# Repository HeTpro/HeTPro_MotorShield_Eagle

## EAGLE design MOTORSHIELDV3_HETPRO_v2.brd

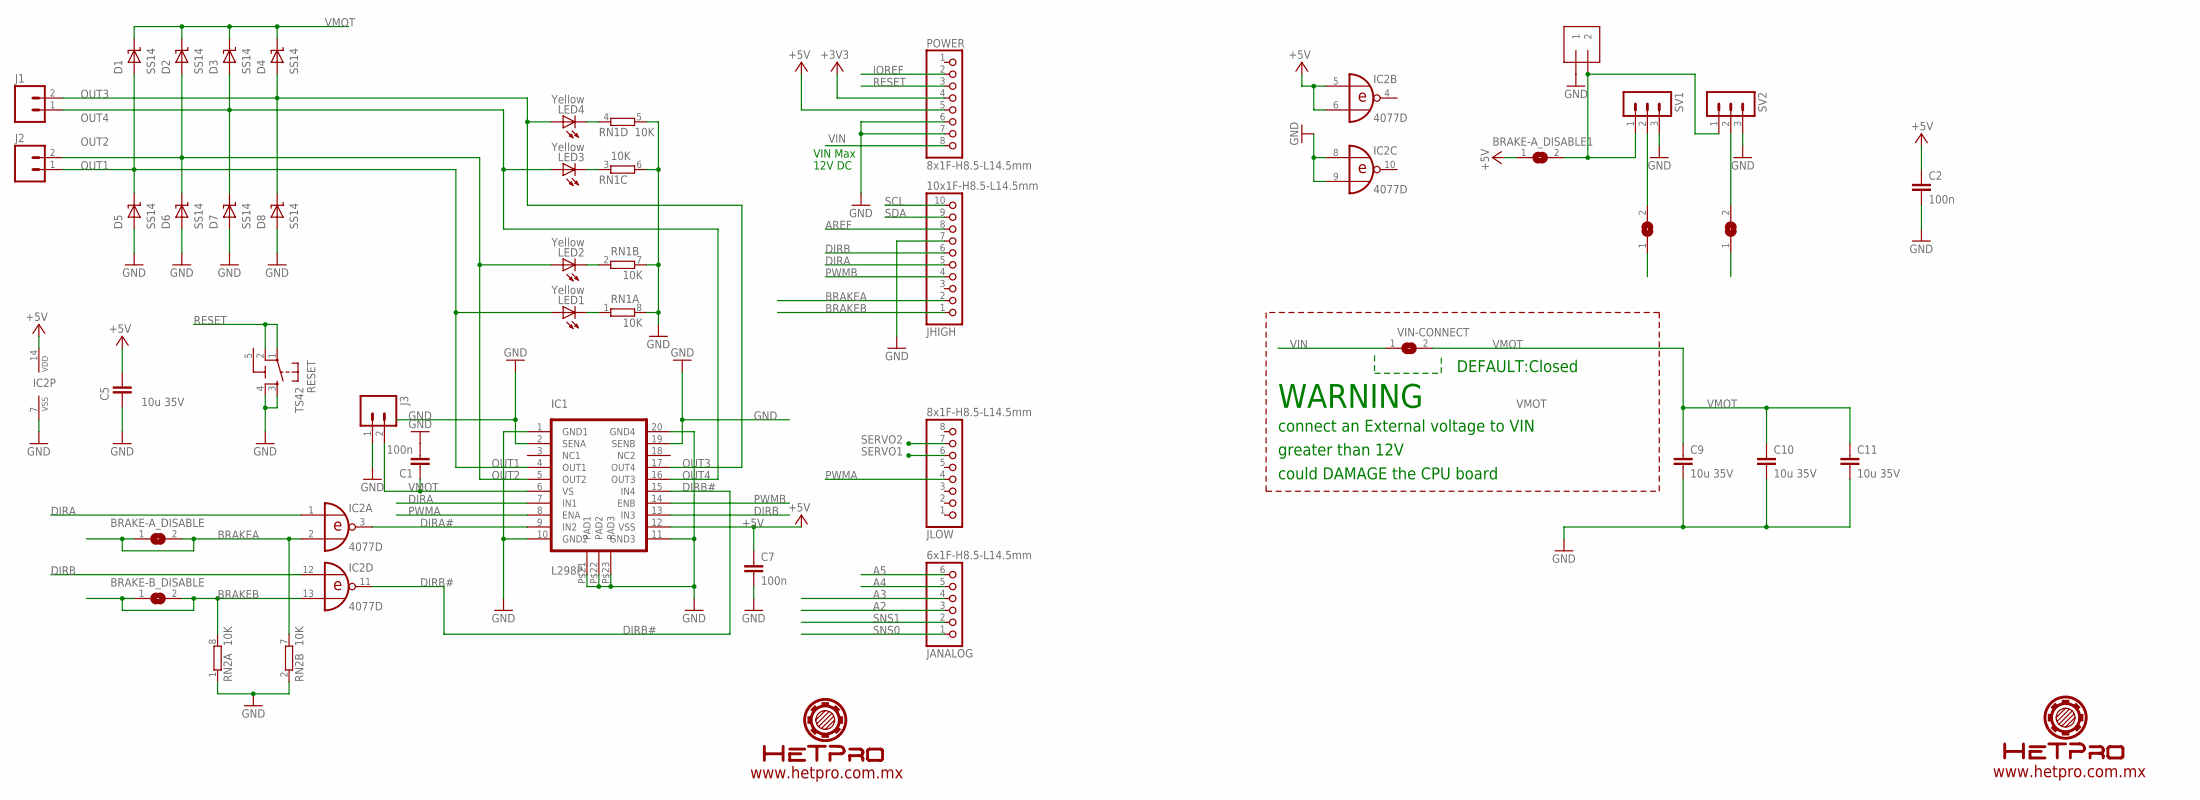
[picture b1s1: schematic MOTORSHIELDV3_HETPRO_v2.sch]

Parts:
BRAKE-A_DISABLE, BRAKE-A_DISABLE1, BRAKE-A_DISABLE2, BRAKE-A_DISABLE3: SJ
BRAKE-B_DISABLE: SJ
C1, C2, C7: 100n; C0603
C5, C9, C10, C11: 10u 35V; C1210
D1, D2, D3, D4, D5, D6, D7, D8: SS14; SMA
IC1: L298P; POWER-SO20
IC2: 4077D; SO14
J1, J2, J3: M025MM; SCREWTERMINAL-5MM-2
J4: 1X2-3.5MM
JANALOG: 6x1F-H8.5-L14.5mm; 1X06-TH
JHIGH: 10x1F-H8.5-L14.5mm; 1X10-TH
JLOW: 8x1F-H8.5-L14.5mm; 1X08-TH
LED1, LED2, LED3, LED4: Yellow; LED-1206
POWER: 8x1F-H8.5-L14.5mm; 1X08-TH
RESET: TS42
RN1, RN2: 10K; CAY16
SV1, SV2: MA03-1
VIN-CONNECT: SJ

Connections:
5-GND: RESET.5 (5-GND)
+3V3: POWER.4
+5V: BRAKE-A_DISABLE1.1, C2.1, C5.1, C7.1, IC1.P$12 (VSS), IC2.5 (I0), IC2.6 (I1), IC2.14 (VDD), POWER.5
A2: JANALOG.3
A3: JANALOG.4
A4: JANALOG.5
A5: JANALOG.6
AREF: JHIGH.8
BRAKEA: BRAKE-A_DISABLE.1, BRAKE-A_DISABLE.2, IC2.2 (I1), JHIGH.2, RN2.7 (2)
BRAKEB: BRAKE-B_DISABLE.1, BRAKE-B_DISABLE.2, IC2.13 (I1), JHIGH.1, RN2.8 (2)
DIRA: IC1.P$7 (IN1), IC2.1 (I0), JHIGH.5
DIRA#: IC1.P$9 (IN2), IC2.3 (O)
DIRB: IC1.P$13 (IN3), IC2.12 (I0), JHIGH.6
DIRB#: IC1.P$15 (IN4), IC2.11 (O)
GND: C1.2, C2.2, C5.2, C7.2, C9.2, C10.2, C11.2, D5.P$2 (A), D6.P$2 (A), D7.P$2 (A), D8.P$2 (A), IC1.P$1 (GND1), IC1.P$2 (SENA), IC1.P$10 (GND2), IC1.P$11 (GND3), IC1.P$19 (SENB), IC1.P$20 (GND4), IC1.P$21 (PAD1), IC1.P$22 (PAD2), IC1.P$23 (PAD3), IC2.7 (VSS), IC2.8 (I0), IC2.9 (I1), J3.1, J4.1, JHIGH.7, POWER.6, POWER.7, RESET.3, RESET.4, RN1.5 (2), RN1.6 (2), RN1.7 (2), RN1.8 (2), RN2.1, RN2.2 (1), SV1.3, SV2.3
IOREF: POWER.2
unnamed: LED4.C, RN1.4 (1)
unnamed: LED3.C, RN1.3 (1)
unnamed: LED2.C, RN1.2 (1)
unnamed: LED1.C, RN1.1
unnamed: BRAKE-A_DISABLE1.2, J4.2, SV1.1, SV2.1
unnamed: BRAKE-A_DISABLE2.2, SV1.2
unnamed: BRAKE-A_DISABLE3.2, SV2.2
OUT1: D1.P$2 (A), D5.P$1 (K), IC1.P$4 (OUT1), J2.1, LED1.A
OUT2: D2.P$2 (A), D6.P$1 (K), IC1.P$5 (OUT2), J2.2, LED2.A
OUT3: D4.P$2 (A), D8.P$1 (K), IC1.P$17 (OUT4), J1.2, LED4.A
OUT4: D3.P$2 (A), D7.P$1 (K), IC1.P$16 (OUT3), J1.1, LED3.A
PWMA: IC1.P$8 (ENA), JLOW.4
PWMB: IC1.P$14 (ENB), JHIGH.4
RESET: POWER.3, RESET.1, RESET.2
SCL: JHIGH.10
SDA: JHIGH.9
SERVO1: BRAKE-A_DISABLE2.1, JLOW.6
SERVO2: BRAKE-A_DISABLE3.1, JLOW.7
SNS0: JANALOG.1
SNS1: JANALOG.2
VIN: POWER.8, VIN-CONNECT.1
VMOT: C1.1, C9.1, C10.1, C11.1, D1.P$1 (K), D2.P$1 (K), D3.P$1 (K), D4.P$1 (K), IC1.P$6 (VS), J3.2, VIN-CONNECT.2

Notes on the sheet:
VIN Max
12V DC
WARNING
connect an External voltage to VIN
greater than 12V
could DAMAGE the CPU board
DEFAULT:Closed
www.hetpro.com.mx

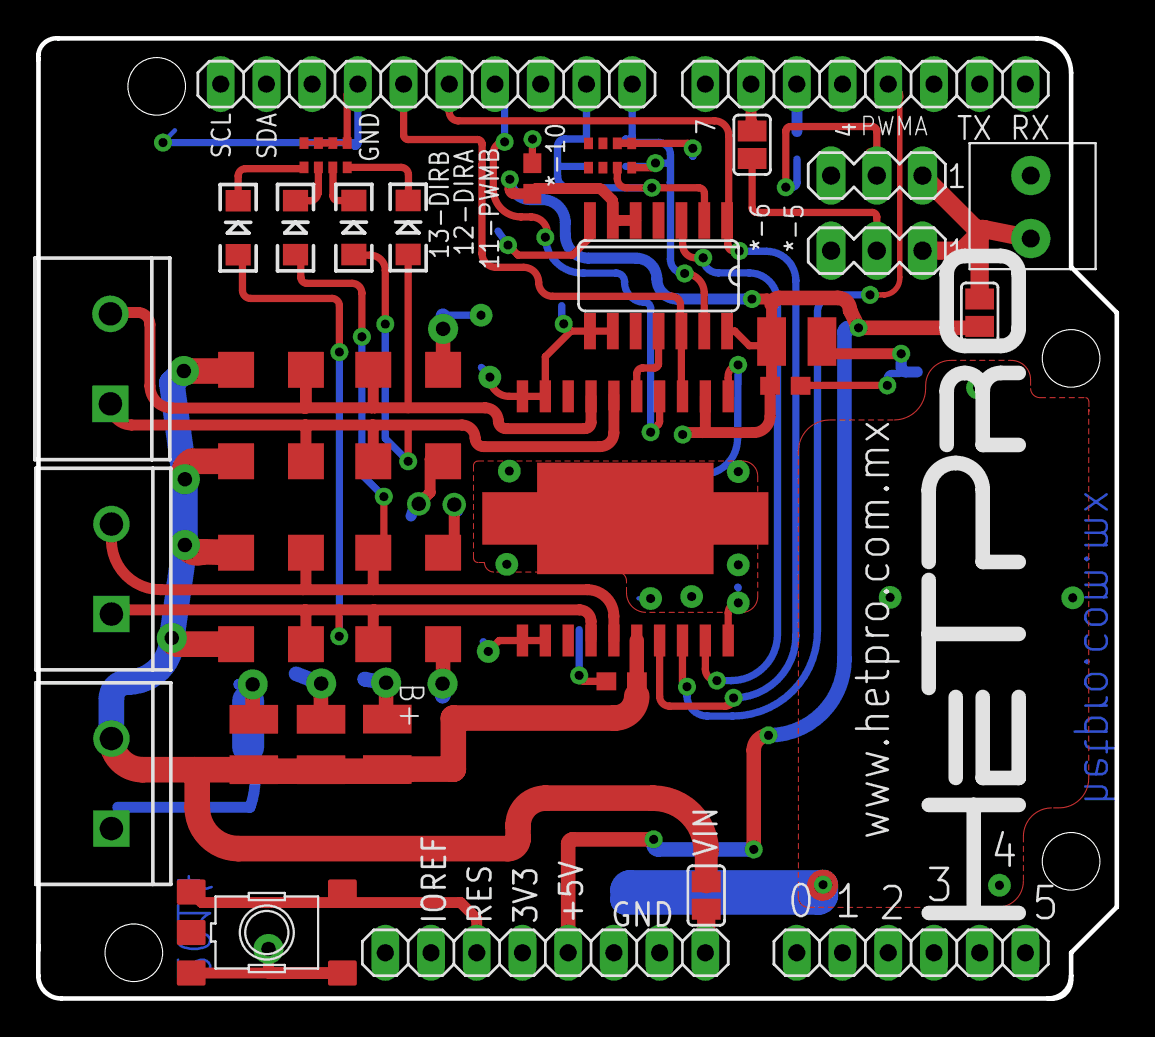
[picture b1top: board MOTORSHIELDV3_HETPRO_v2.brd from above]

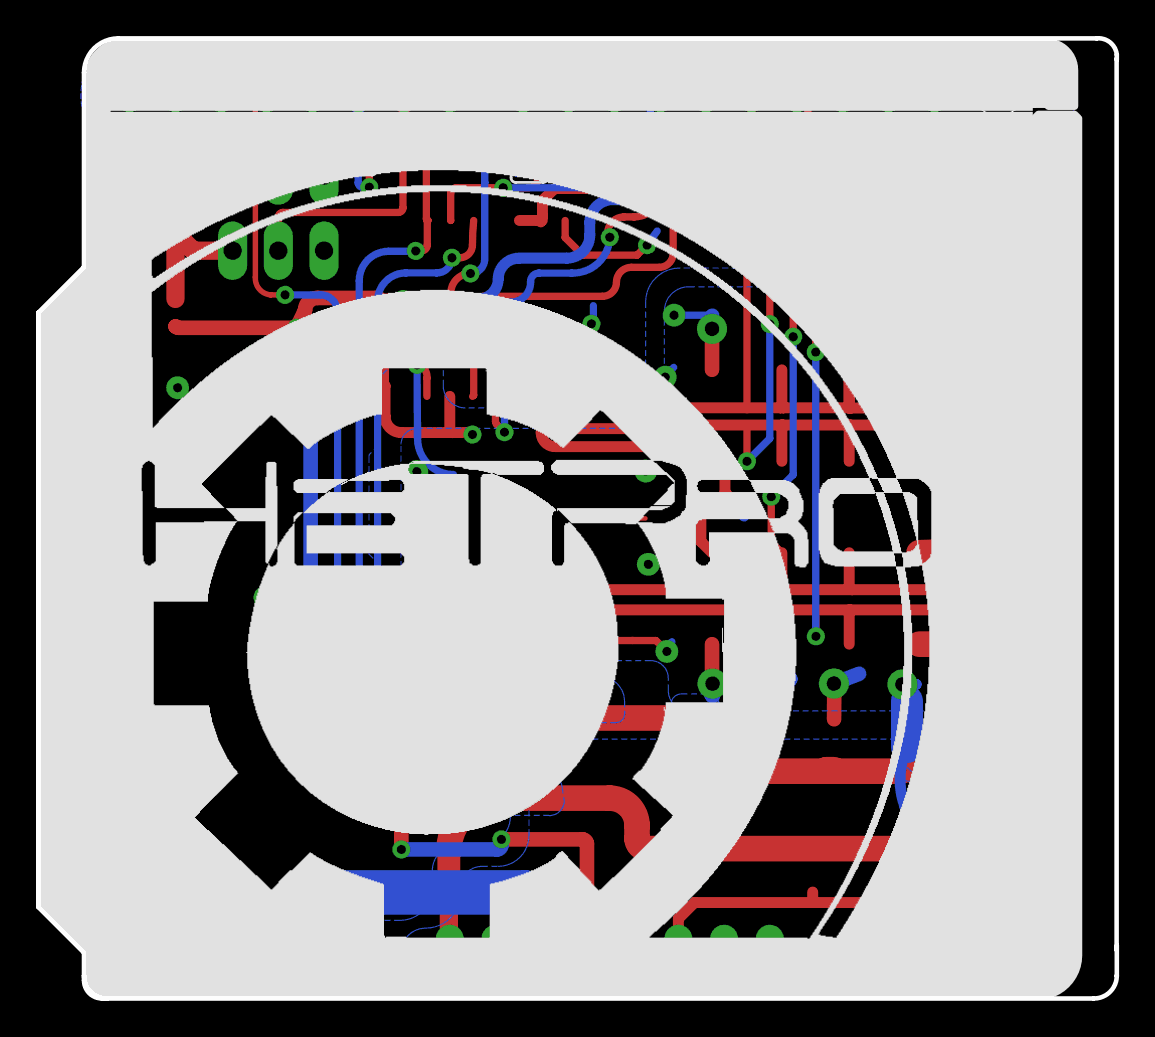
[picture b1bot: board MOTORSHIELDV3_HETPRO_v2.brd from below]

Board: 2 copper layers, 59.9 x 53.3 mm, 40 parts (3 on the bottom side), 26 nets.

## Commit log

2014-10-15 :octocat: Added .gitattributes & .gitignore files
2014-10-15 Archivos añadidos
    A

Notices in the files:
parts and their libraries:
SparkFun: Licensing: CC v3.0 Share-Alike You are welcome to use this library for commercial purposes.
